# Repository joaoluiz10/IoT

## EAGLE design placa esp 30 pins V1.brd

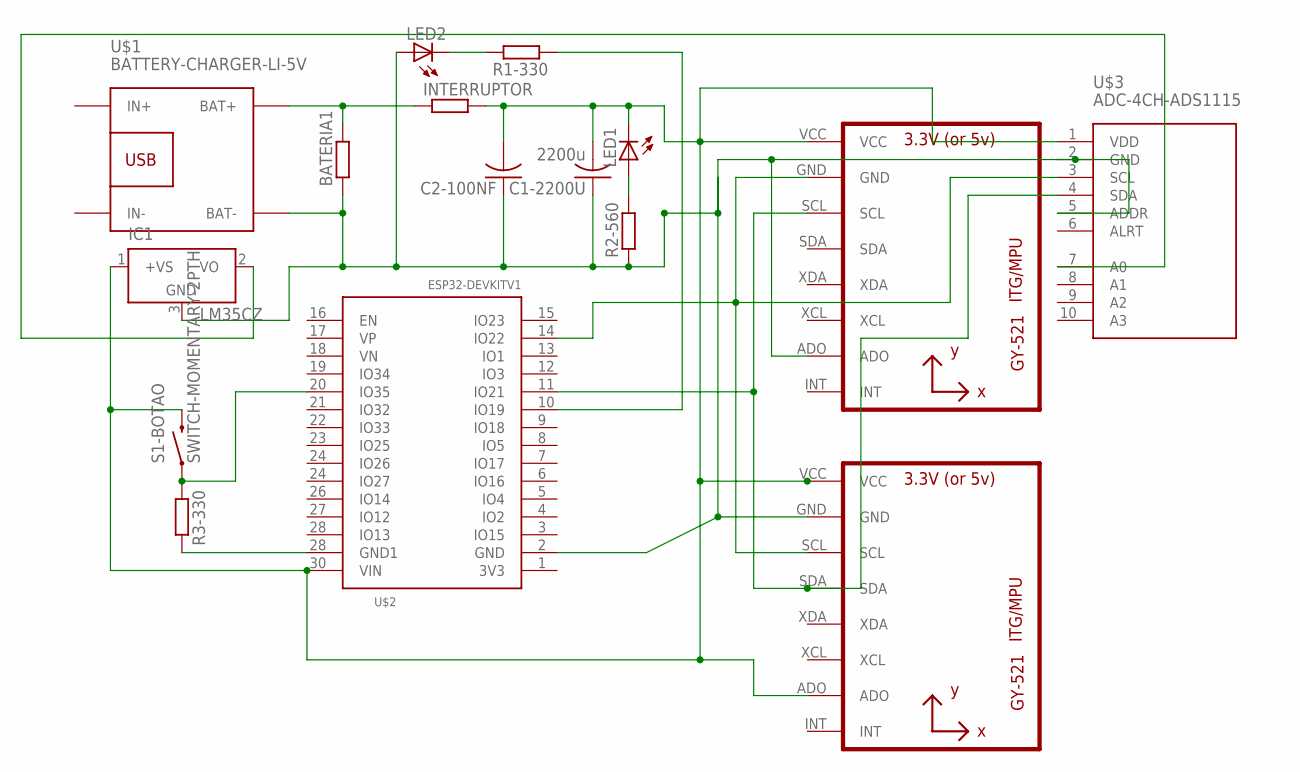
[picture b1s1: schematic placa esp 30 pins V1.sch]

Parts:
BATERIA1: R-EU_0207/10; 0207/10
C1-2200U: 2200u; C025-060X050
C2-100NF: C-US025-060X050; C025-060X050
IC1: LM35CZ; TO92
INTERRUPTOR: R-EU_0207/7; 0207/7
LED1, LED2: LEDLD260; LD260
OXIMETRO: GY-521MPU6050; GY-521
R1-330, R2-560, R3-330: R-EU_0207/10; 0207/10
S1-BOTAO: SWITCH-MOMENTARY-2PTH; TACTILE-PTH
U2: GY-521MPU6050; GY-521
U$1: BATTERY-CHARGER-LI-5V
U$2: ESP32DEVKITV1; ESP32-DEVKITV1
U$3: ADC-4CH-ADS1115

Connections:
unnamed: C1-2200U.2, C2-100NF.2, IC1.1 (+VS), INTERRUPTOR.2, LED1.K (C), OXIMETRO.VCC, S1-BOTAO.3 (2), U2.ADO, U2.VCC, U$2.30 (VIN), U$3.1 (VDD)
unnamed: OXIMETRO.GND, U2.SCL, U$2.14 (IO22), U$3.3 (SCL)
unnamed: R3-330.1, S1-BOTAO.1, U$2.20 (IO35)
unnamed: IC1.2 (VO), U$3.7 (A0)
unnamed: OXIMETRO.SCL, U2.SDA, U$2.11 (IO21), U$3.4 (SDA)
unnamed: R3-330.2, U$2.28 (IO13)
unnamed: LED1.A, R2-560.2
unnamed: BATERIA1.2, INTERRUPTOR.1, U$1.BAT+
unnamed: LED2.K (C), R1-330.2
unnamed: BATERIA1.1, C1-2200U.1, C2-100NF.1, IC1.3 (GND), LED2.A, OXIMETRO.ADO, R2-560.1, U2.GND, U$1.BAT-, U$2.2 (GND), U$3.2 (GND), U$3.5 (ADDR)
unnamed: R1-330.1, U$2.10 (IO19)

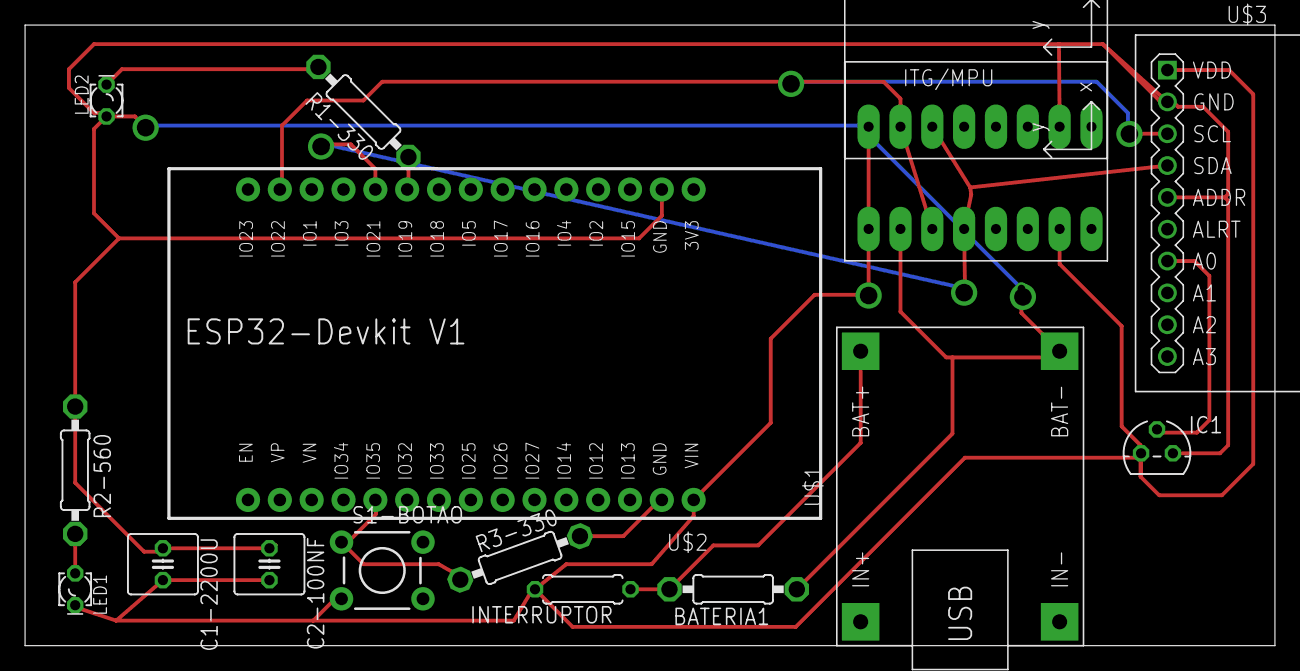
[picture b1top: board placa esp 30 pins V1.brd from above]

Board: 2 copper layers, 99.7 x 49.5 mm, 16 parts (0 on the bottom side), 11 nets.

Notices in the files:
parts and their libraries:
diy-modules: Released under the Creative Commons Attribution 4.0 International License: http://creativecommons.org/licenses/by/4.0
SparkFun-Electromechanical: Licensing: Creative Commons ShareAlike 4.0 International - https://creativecommons.org/licenses/by-sa/4.0
